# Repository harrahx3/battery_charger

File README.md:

# battery_charger

PCB design KiCad project

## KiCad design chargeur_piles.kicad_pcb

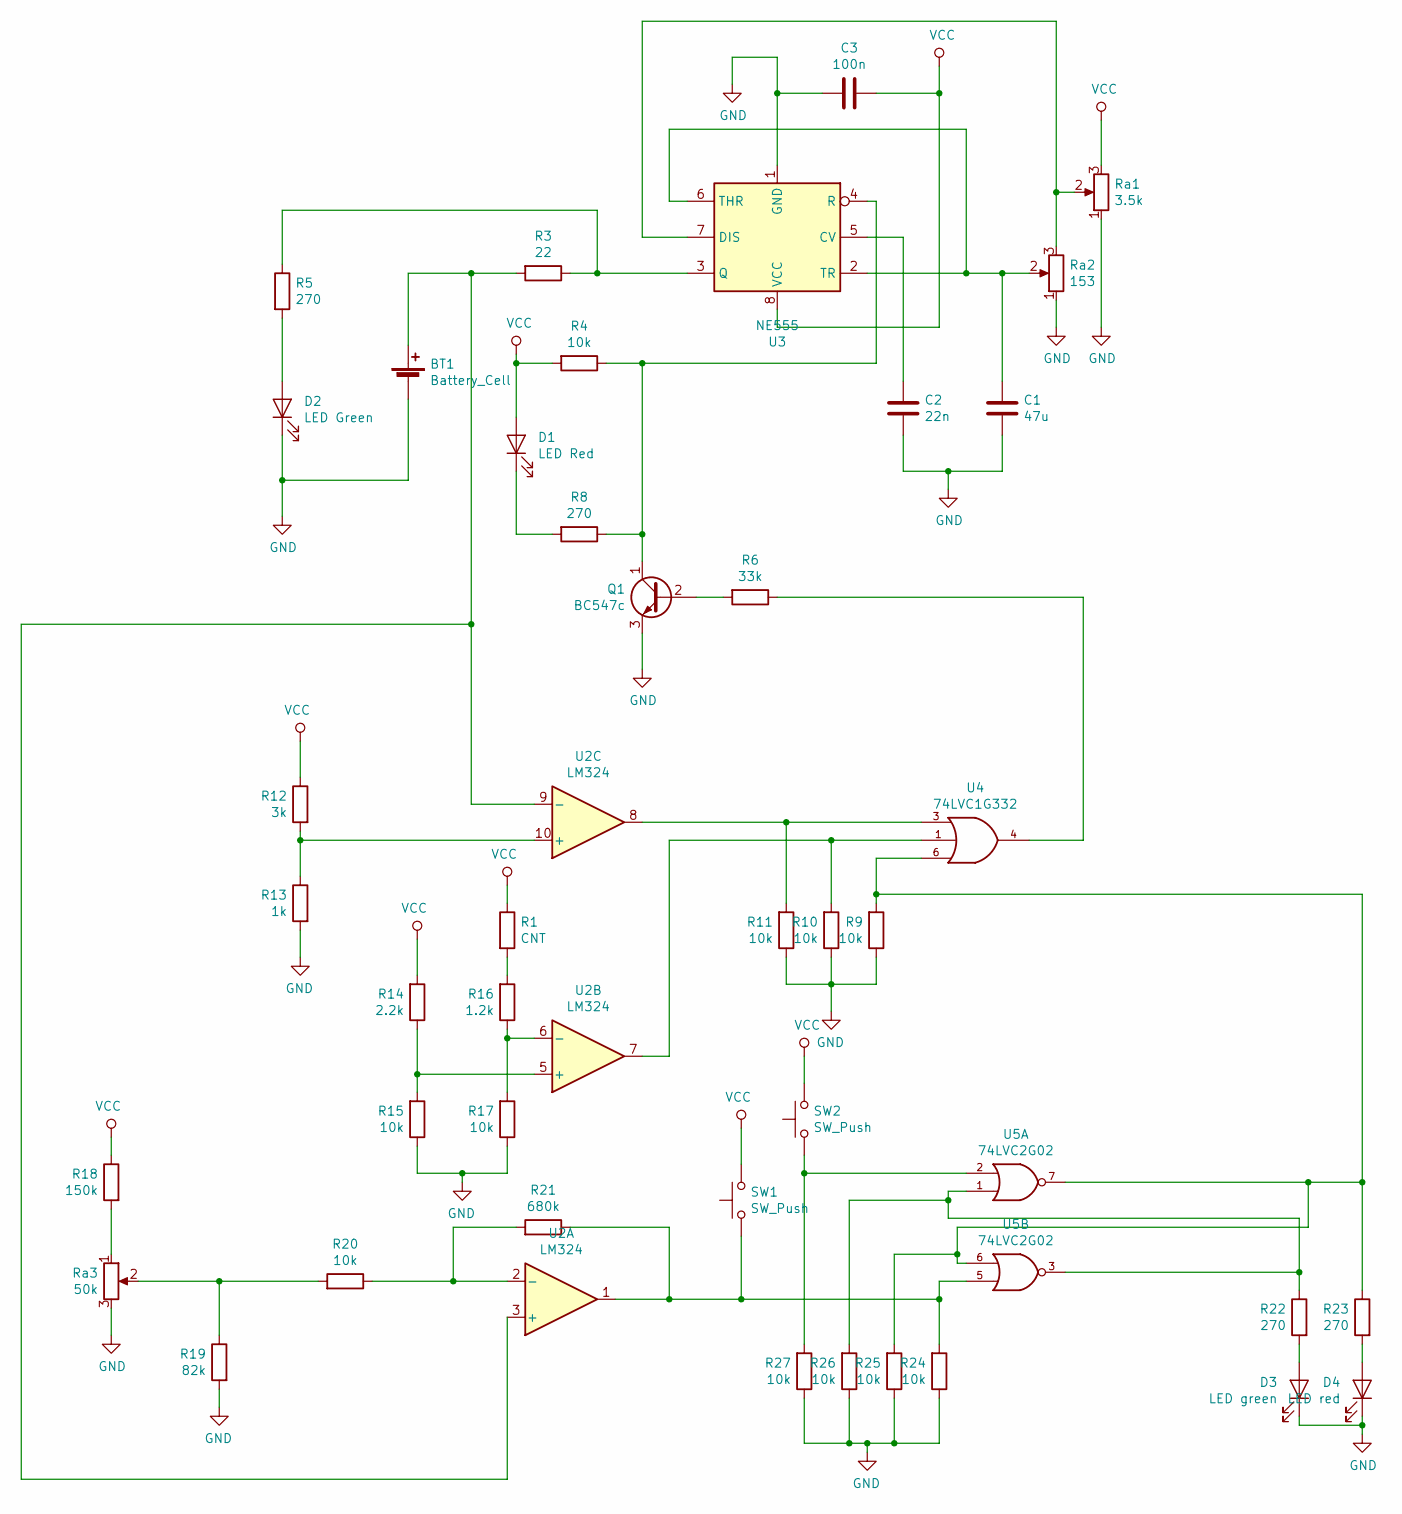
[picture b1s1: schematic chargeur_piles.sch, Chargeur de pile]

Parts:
BT1: Battery_Cell; BatteryHolder_Keystone_2466_1xAAA
C1: 47u; C_Radial_D6.3mm_H11.0mm_P2.50mm
C2: 22n; C_Disc_D6.0mm_W4.4mm_P5.00mm
C3: 100n; C_Radial_D12.5mm_H20.0mm_P5.00mm
D1: LED Red; LED_0805_2012Metric_Pad1.15x1.40mm_HandSolder
D2: LED Green; LED_0805_2012Metric_Pad1.15x1.40mm_HandSolder
D3: LED green; LED_0805_2012Metric_Pad1.15x1.40mm_HandSolder
D4: LED red; LED_0805_2012Metric_Pad1.15x1.40mm_HandSolder
Q1: BC547c; TO-92_Inline
R1: CNT; R_Axial_DIN0918_L18.0mm_D9.0mm_P25.40mm_Horizontal
R3: 22; R_0805_2012Metric_Pad1.15x1.40mm_HandSolder
R4, R9, R10, R11, R15, R17, R20, R24, R25, R26, R27: 10k; R_0805_2012Metric_Pad1.15x1.40mm_HandSolder
R5, R8, R22, R23: 270; R_0805_2012Metric_Pad1.15x1.40mm_HandSolder
R6: 33k; R_0805_2012Metric_Pad1.15x1.40mm_HandSolder
R12: 3k; R_0805_2012Metric_Pad1.15x1.40mm_HandSolder
R13: 1k; R_0805_2012Metric_Pad1.15x1.40mm_HandSolder
R14: 2.2k; R_0805_2012Metric_Pad1.15x1.40mm_HandSolder
R16: 1.2k; R_0805_2012Metric_Pad1.15x1.40mm_HandSolder
R18: 150k; R_0805_2012Metric_Pad1.15x1.40mm_HandSolder
R19: 82k; R_0805_2012Metric_Pad1.15x1.40mm_HandSolder
R21: 680k; R_0805_2012Metric_Pad1.15x1.40mm_HandSolder
Ra1: 3.5k; Potentiometer_ACP_CA6-H2,5_Horizontal
Ra2: 153; Potentiometer_ACP_CA6-H2,5_Horizontal
Ra3: 50k; Potentiometer_ACP_CA6-H2,5_Horizontal
SW1, SW2: SW_Push; SW_PUSH-12mm
U2: LM324; DIP-14_W7.62mm_Socket
U3: NE555; DIP-8_W7.62mm_Socket
U4: 74LVC1G332; SOT-23-6_Handsoldering
U5: 74LVC2G02; SSOP-8_5.25x5.24mm_P1.27mm

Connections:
GND: BT1.2 (-), C1.2, C2.2, C3.2, D2.1 (K), D3.1 (K), D4.1 (K), Q1.3 (E), R9.1, R10.1, R11.1, R13.2, R15.1, R17.1, R19.2, R24.1, R25.1, R26.1, R27.1, Ra1.1, Ra2.1, Ra3.3, U3.1 (GND), U4.2 (GND), U5.4 (GND)
unnamed: BT1.1 (+), R3.2, U2.3 (+), U2.9 (-)
unnamed: C1.1, Ra2.2, U3.2 (TR), U3.6 (THR)
unnamed: C2.1, U3.5 (CV)
unnamed: D1.1 (K), R8.2
unnamed: D2.2 (A), R5.2
unnamed: D3.2 (A), R22.2
unnamed: D4.2 (A), R23.2
unnamed: Q1.1 (C), R4.1, R8.1, U3.4 (R)
unnamed: Q1.2 (B), R6.2
unnamed: R1.2, R16.2
unnamed: R3.1, R5.1, U3.3 (Q)
unnamed: R6.1, U4.4
unnamed: R10.2, U2.7, U4.1
unnamed: R11.2, U2.8, U4.3
unnamed: R12.2, R13.1, U2.10 (+)
unnamed: R14.1, R15.2, U2.5 (+)
unnamed: R16.1, R17.2, U2.6 (-)
unnamed: R18.2, Ra3.1
unnamed: R19.1, R20.2, Ra3.2
unnamed: R20.1, R21.2, U2.2 (-)
unnamed: R21.1, R24.2, SW1.1, U2.1, U5.5
unnamed: R22.1, R26.2, U5.1, U5.3
unnamed: R9.2, R23.1, R25.2, U4.6, U5.6, U5.7
unnamed: R27.2, SW2.1, U5.2
unnamed: Ra1.2, Ra2.3, U3.7 (DIS)
VCC: C3.1, D1.2 (A), R1.1, R4.2, R12.1, R14.2, R18.1, Ra1.3, SW1.2, SW2.2, U3.8 (VCC), U4.5 (VCC), U5.8 (VCC)

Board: 2 copper layers, 43 parts (0 on the bottom side), 27 nets, no tracks yet.
